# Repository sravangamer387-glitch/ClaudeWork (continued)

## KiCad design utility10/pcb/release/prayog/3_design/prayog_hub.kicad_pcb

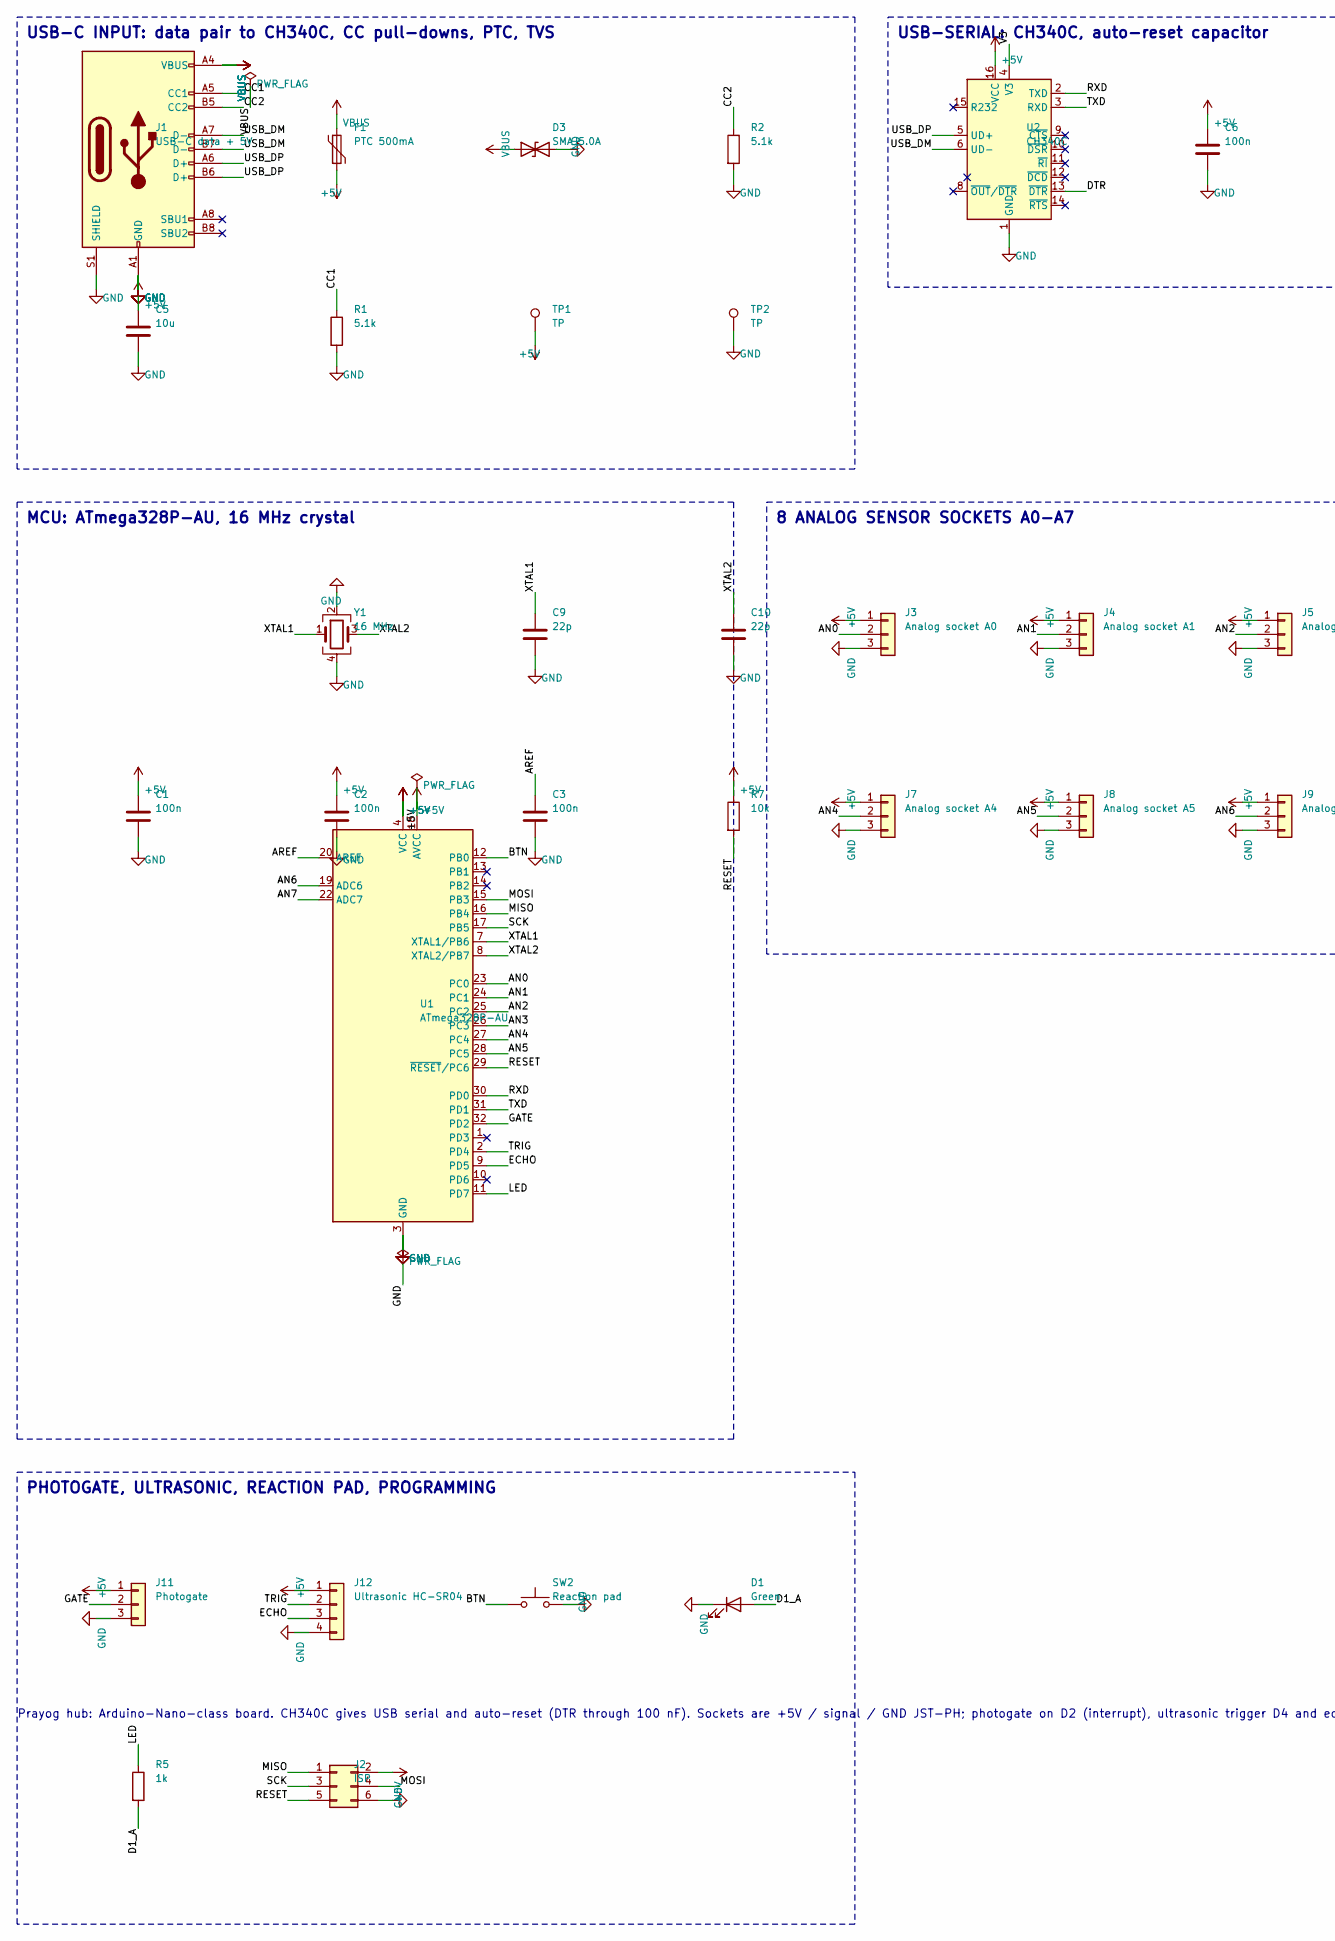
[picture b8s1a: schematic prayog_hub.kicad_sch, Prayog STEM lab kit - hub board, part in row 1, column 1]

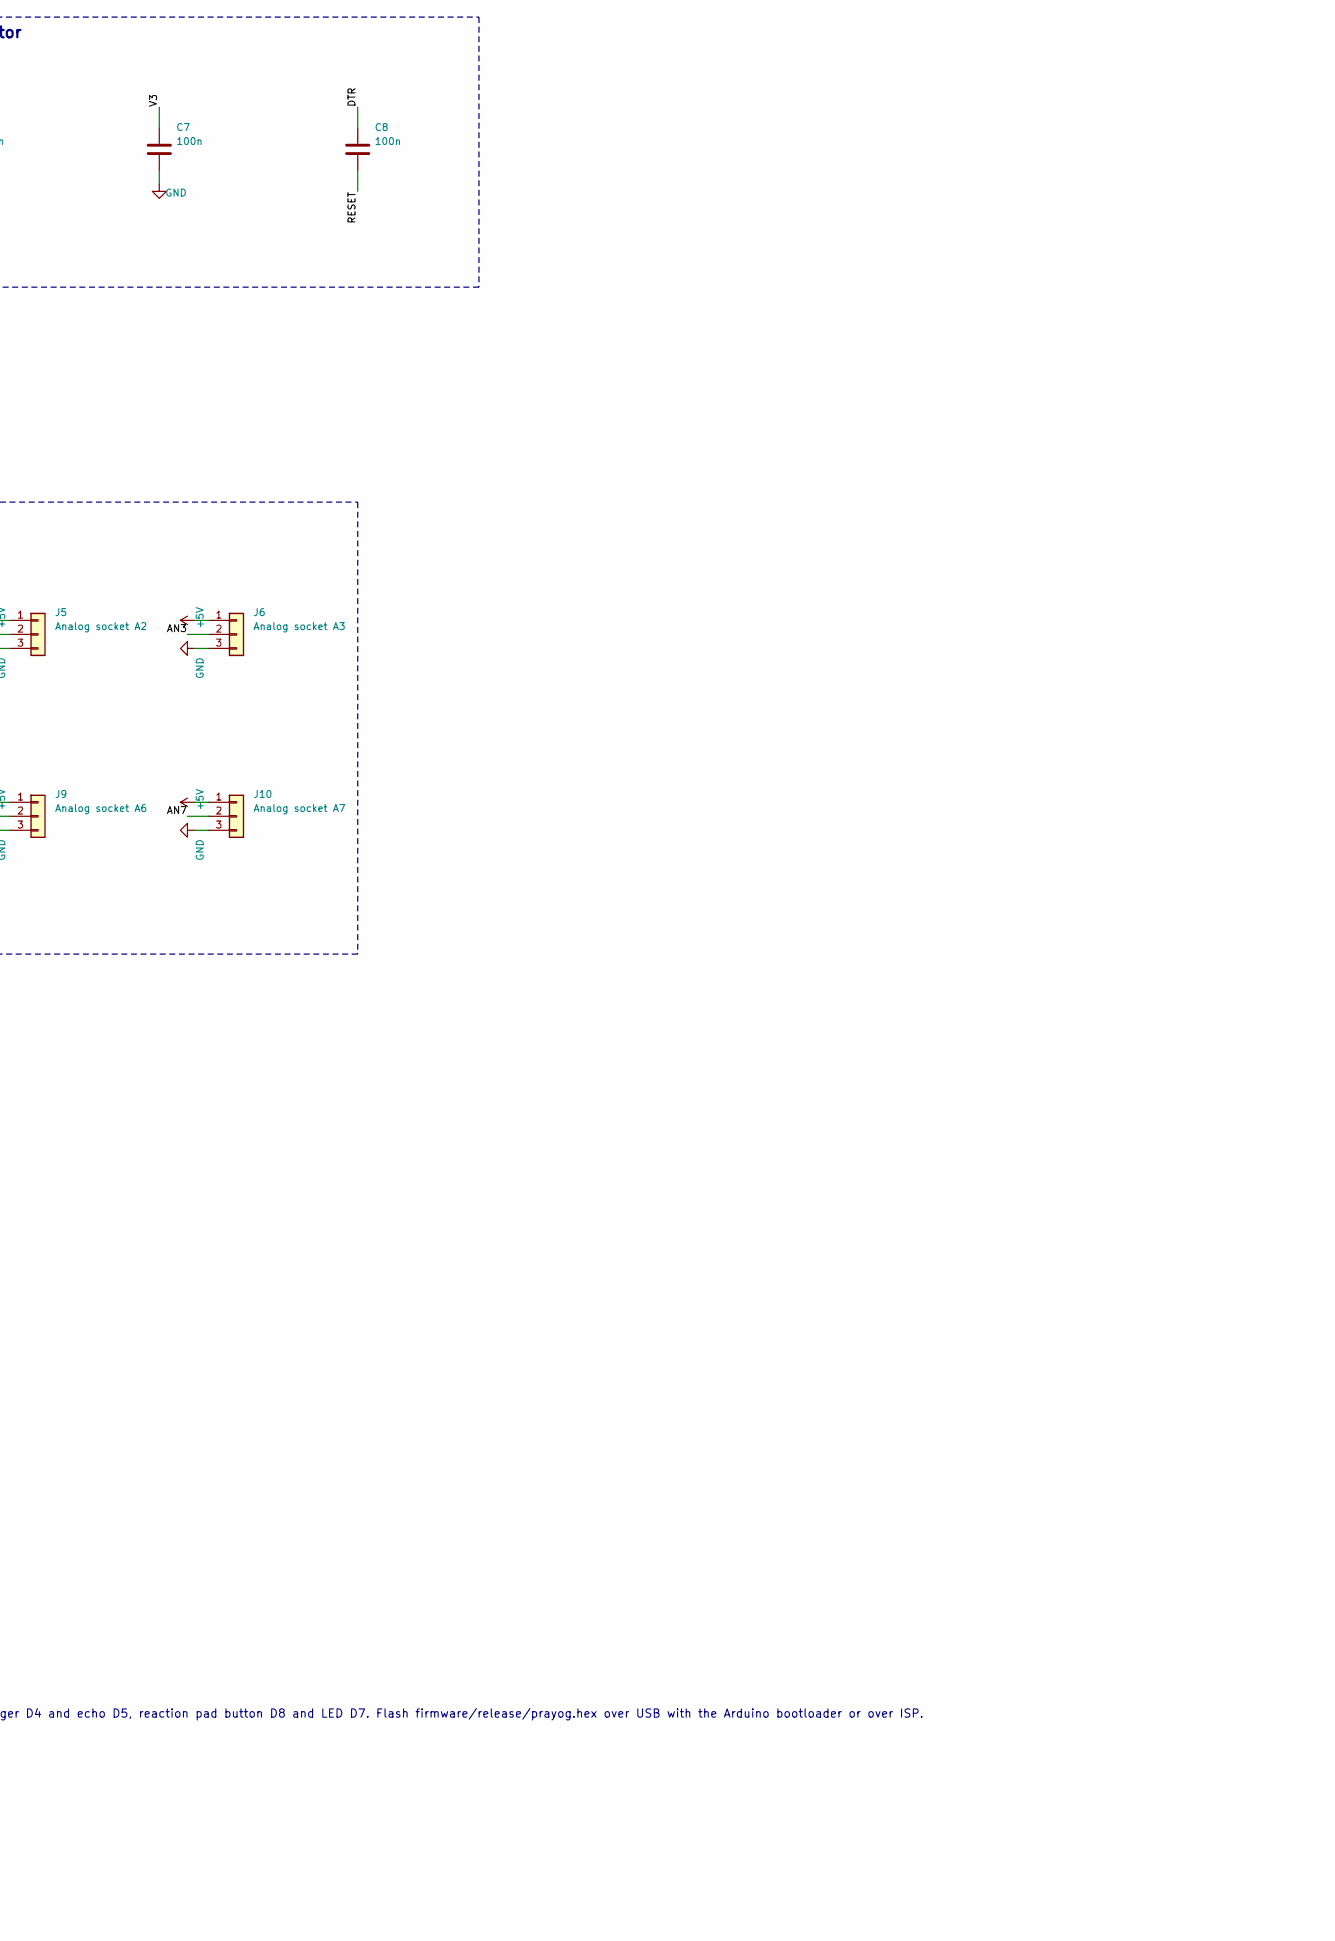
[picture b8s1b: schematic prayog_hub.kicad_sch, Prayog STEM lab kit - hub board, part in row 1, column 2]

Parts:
C1, C2, C3, C6, C7, C8: 100n; C_0603_1608Metric
C5: 10u; C_0805_2012Metric
C9, C10: 22p; C_0603_1608Metric
D1: Green; LED_0603_1608Metric
D3: SMAJ5.0A; D_SMA
F1: PTC 500mA; Fuse_1206_3216Metric
J1: USB-C data + 5V; USB_C_Receptacle_HRO_TYPE-C-31-M-12
J2: ISP; PinHeader_2x03_P2.54mm_Vertical
J3: Analog socket A0; JST_PH_B3B-PH-K_1x03_P2.00mm_Vertical
J4: Analog socket A1; JST_PH_B3B-PH-K_1x03_P2.00mm_Vertical
J5: Analog socket A2; JST_PH_B3B-PH-K_1x03_P2.00mm_Vertical
J6: Analog socket A3; JST_PH_B3B-PH-K_1x03_P2.00mm_Vertical
J7: Analog socket A4; JST_PH_B3B-PH-K_1x03_P2.00mm_Vertical
J8: Analog socket A5; JST_PH_B3B-PH-K_1x03_P2.00mm_Vertical
J9: Analog socket A6; JST_PH_B3B-PH-K_1x03_P2.00mm_Vertical
J10: Analog socket A7; JST_PH_B3B-PH-K_1x03_P2.00mm_Vertical
J11: Photogate; JST_PH_B3B-PH-K_1x03_P2.00mm_Vertical
J12: Ultrasonic HC-SR04; JST_PH_B4B-PH-K_1x04_P2.00mm_Vertical
R1, R2: 5.1k; R_0603_1608Metric
R5: 1k; R_0603_1608Metric
R7: 10k; R_0603_1608Metric
SW2: Reaction pad; SW_SPST_B3U-1000P
TP1, TP2: TP; TestPoint_Pad_D1.5mm
U1: ATmega328P-AU; TQFP-32_7x7mm_P0.8mm
U2: CH340C; SOIC-16_3.9x9.9mm_P1.27mm
Y1: 16 MHz; Crystal_SMD_3225-4Pin_3.2x2.5mm

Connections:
+5V: C1.1, C2.1, C5.1, C6.1, F1.2, J2.2, J3.1, J4.1, J5.1, J6.1, J7.1, J8.1, J9.1, J10.1, J11.1, J12.1, R7.1, TP1.1, U1.4 (VCC), U1.6 (VCC), U1.18 (AVCC), U2.16 (VCC)
AN0: J3.2, U1.23 (PC0)
AN1: J4.2, U1.24 (PC1)
AN2: J5.2, U1.25 (PC2)
AN3: J6.2, U1.26 (PC3)
AN4: J7.2, U1.27 (PC4)
AN5: J8.2, U1.28 (PC5)
AN6: J9.2, U1.19 (ADC6)
AN7: J10.2, U1.22 (ADC7)
AREF: C3.1, U1.20 (AREF)
BTN: SW2.1, U1.12 (PB0)
CC1: J1.A5 (CC1), R1.1
CC2: J1.B5 (CC2), R2.1
D1_A: D1.2 (A), R5.2
DTR: C8.1, U2.13 (~DTR)
ECHO: J12.3, U1.9 (PD5)
GATE: J11.2, U1.32 (PD2)
GND: C1.2, C2.2, C3.2, C5.2, C6.2, C7.2, C9.2, C10.2, D1.1 (K), D3.2 (A2), J1.A1 (GND), J1.A12 (GND), J1.B1 (GND), J1.B12 (GND), J1.S1 (SHIELD), J2.6, J3.3, J4.3, J5.3, J6.3, J7.3, J8.3, J9.3, J10.3, J11.3, J12.4, R1.2, R2.2, SW2.2, TP2.1, U1.3 (GND), U1.5 (GND), U1.21 (GND), U2.1 (GND), Y1.2, Y1.4
LED: R5.1, U1.11 (PD7)
MISO: J2.1, U1.16 (PB4)
MOSI: J2.4, U1.15 (PB3)
RESET: C8.2, J2.5, R7.2, U1.29 (~RESET/PC6)
RXD: U1.30 (PD0), U2.2 (TXD)
SCK: J2.3, U1.17 (PB5)
TRIG: J12.2, U1.2 (PD4)
TXD: U1.31 (PD1), U2.3 (RXD)
USB_DM: J1.A7 (D-), J1.B7 (D-), U2.6 (UD-)
USB_DP: J1.A6 (D+), J1.B6 (D+), U2.5 (UD+)
V3: C7.1, U2.4 (V3)
VBUS: D3.1 (A1), F1.1, J1.A4 (VBUS), J1.A9 (VBUS), J1.B4 (VBUS), J1.B9 (VBUS)
XTAL1: C9.1, U1.7 (XTAL1/PB6), Y1.1
XTAL2: C10.1, U1.8 (XTAL2/PB7), Y1.3

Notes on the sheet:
USB-C INPUT: data pair to CH340C, CC pull-downs, PTC, TVS
USB-SERIAL: CH340C, auto-reset capacitor
MCU: ATmega328P-AU, 16 MHz crystal
8 ANALOG SENSOR SOCKETS A0-A7
PHOTOGATE, ULTRASONIC, REACTION PAD, PROGRAMMING
Prayog hub: Arduino-Nano-class board. CH340C gives USB serial and auto-reset (DTR through 100 nF). Sockets are +5V / signal / GND JST-PH; photogate on D2 (interrupt), ultrasonic trigger D4 and echo D5, reaction pad button D8 and LED D7. Flash firmware/release/prayog.hex over USB with the Arduino bo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

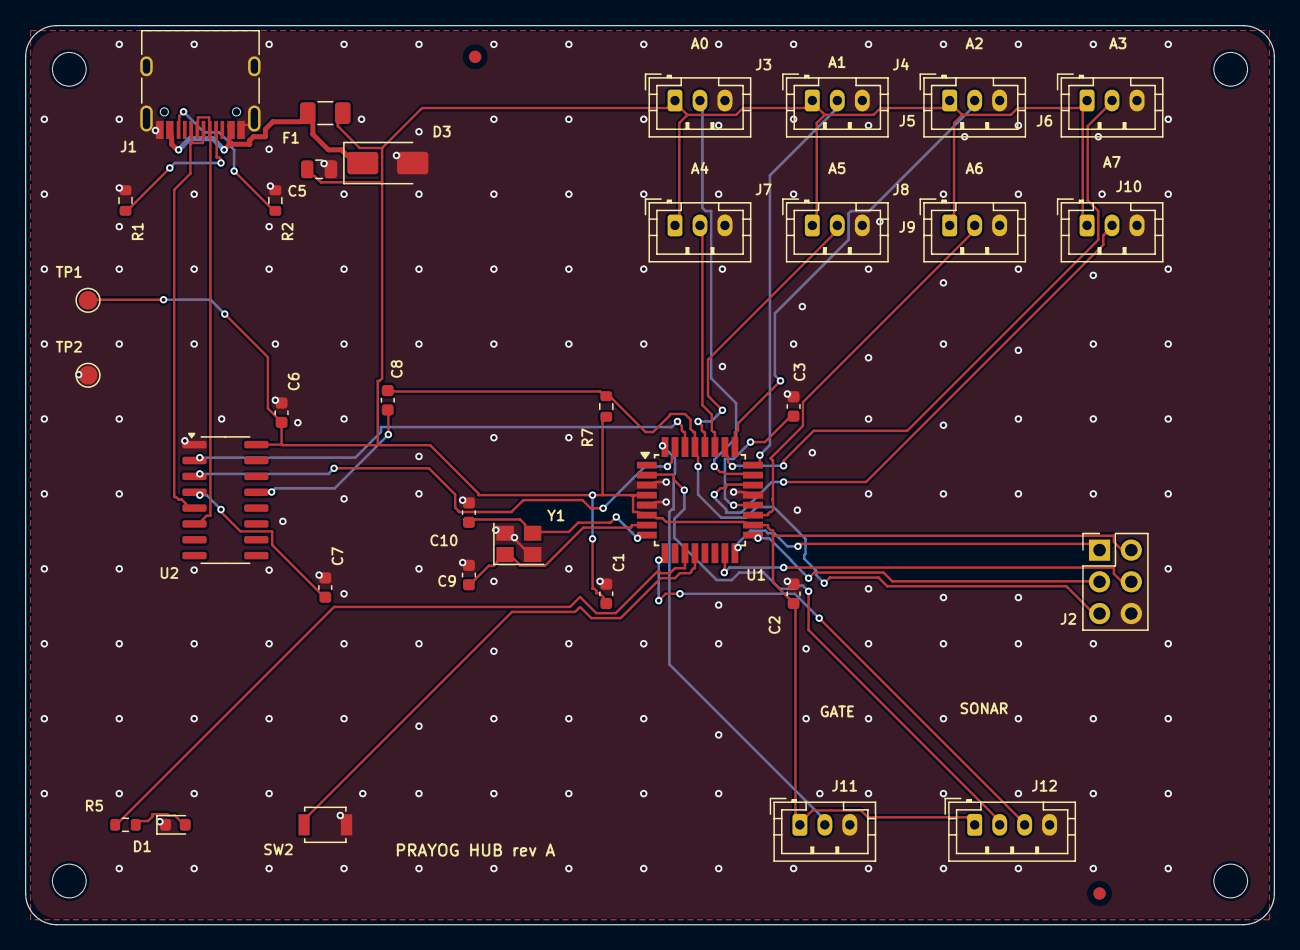
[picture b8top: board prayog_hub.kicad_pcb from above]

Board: 2 copper layers, 100.0 x 72.0 mm, 40 parts (0 on the bottom side), 32 nets.

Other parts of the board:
FID1, FID2: Fiducial; Fiducial_1mm_Mask2mm
H1, H2, H3, H4: M2.5; MountingHole_2.7mm_M2.5

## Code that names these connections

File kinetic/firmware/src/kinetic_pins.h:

/* KINETIC controller (kinetic_ctl rev A) ESP32-S3 pin map: must match utility10/pcb/boards/kinetic_ctl.py */
#pragma once
#define PIN_X_STEP 4
#define PIN_X_DIR  5
#define PIN_X_EN   6
#define PIN_Y_STEP 7
#define PIN_Y_DIR  15
#define PIN_Y_EN   16
#define PIN_Z_STEP 17
#define PIN_Z_DIR  18
#define PIN_Z_EN   8
#define PIN_ES_X   9
#define PIN_ES_Y   10
#define PIN_ES_Z   11
#define PIN_S_CS   12
#define PIN_S_SCLK 13
#define PIN_S_MOSI 14
#define PIN_S_MISO 21
#define PIN_VM_SENSE 1     /* 24 V divider 100k/10k: Vm = adc_volts * 11 */
#define PIN_LED    48
#define PIN_UART_TX 43     /* TXD0 */
#define PIN_UART_RX 44     /* RXD0 */

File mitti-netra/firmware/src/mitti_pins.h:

/* MITTI-NETRA rev A ESP32-S3 pin map: must match utility10/pcb/boards/mitti.py (checked by tools/check_pins.py) */
#pragma once
#define PIN_ONEWIRE 15
#define PIN_MODEM_TX 16       /* net MODEM_TX: ESP32 TX output toward the modem breakout RX */
#define PIN_MODEM_RX 17       /* net MODEM_RX: ESP32 RX input from the modem breakout TX */
#define PIN_MODEM_PWRKEY 18
#define PIN_MODEM_STATUS 8
#define PIN_MODEM_EN 6
#define PIN_HX_DT 4
#define PIN_HX_SCK 5
#define PIN_ACC_INT 9
#define PIN_SDA 10
#define PIN_SCL 11
#define PIN_SOIL_ADC 1
#define PIN_VBAT_ADC 2
#define PIN_LED 48

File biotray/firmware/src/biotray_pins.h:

/* BioTray rev A ESP32-S3 pin map: must match utility10/pcb/boards/biotray.py */
#pragma once
#define PIN_PUMP1 4
#define PIN_PUMP2 5
#define PIN_LIGHT 6     /* PWM, active high gate */
#define PIN_FAN   7
#define PIN_SDA   8
#define PIN_SCL   9
#define PIN_LEVEL 10    /* float switch closes to GND when water present; external 10k pull-up */
#define PIN_ONEWIRE 15
#define PIN_PH_ADC 1    /* 0-3 V pH module output via 1k + 100 nF */
#define PIN_EC_ADC 2
#define PIN_LED   48
